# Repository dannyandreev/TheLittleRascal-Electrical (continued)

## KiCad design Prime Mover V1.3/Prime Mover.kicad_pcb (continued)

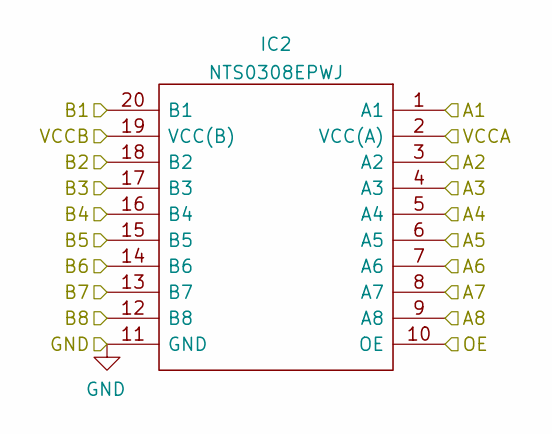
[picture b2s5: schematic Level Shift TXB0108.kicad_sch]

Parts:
IC2: NTS0308EPWJ; SOP65P640X110-20N; Manufacturer_Part_Number NTS0308EPWJ; Mouser Part Number 771-NTS0308EPWJ

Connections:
+3V3: IC2.2 (VCC(A)); also elsewhere on the board
+5V: IC2.19 (VCC(B)); also elsewhere on the board
B3: IC2.17 (B3); also elsewhere on the board
B4: IC2.16 (B4); also elsewhere on the board
B5: IC2.15 (B5); also elsewhere on the board
B6: IC2.14 (B6); also elsewhere on the board
ECHO_3V3: IC2.1 (A1); also elsewhere on the board
ECHO_5V: IC2.20 (B1); also elsewhere on the board
GND: IC2.11 (GND); also elsewhere on the board
GPIO19: IC2.4 (A3); also elsewhere on the board
GPIO20: IC2.5 (A4); also elsewhere on the board
GPIO26: IC2.6 (A5); also elsewhere on the board
GPIO27: IC2.7 (A6); also elsewhere on the board
LVL_OE: IC2.10 (OE); also elsewhere on the board
PWM_ESC: IC2.8 (A7); also elsewhere on the board
PWM_ESC_5V: IC2.13 (B7); also elsewhere on the board
PWM_Servo: IC2.9 (A8); also elsewhere on the board
PWM_Servo_5V: IC2.12 (B8); also elsewhere on the board
TRIG_3V3: IC2.3 (A2); also elsewhere on the board
TRIG_5V: IC2.18 (B2); also elsewhere on the board

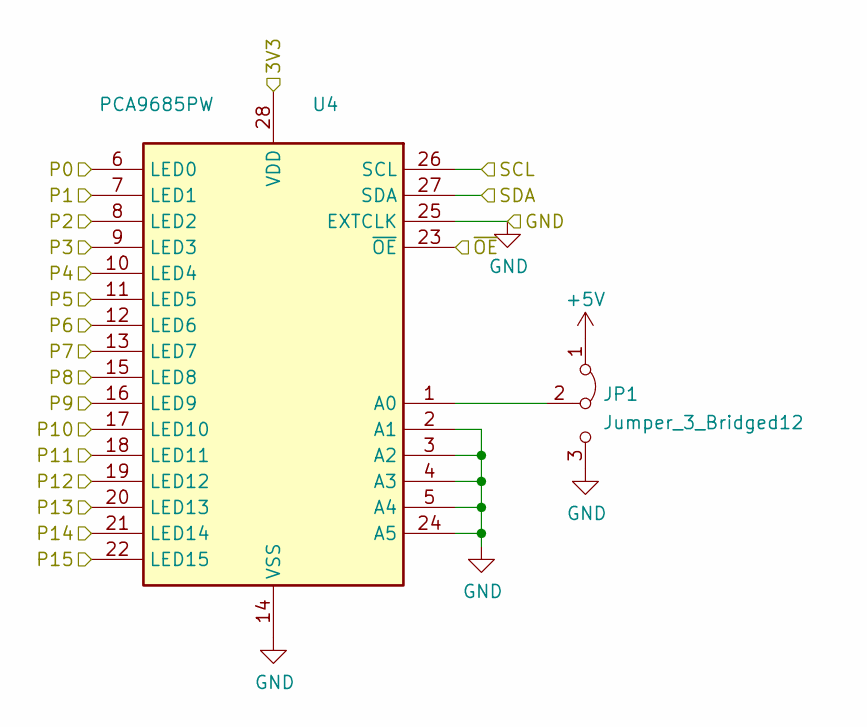
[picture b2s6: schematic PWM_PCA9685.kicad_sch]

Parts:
JP1: Jumper_3_Bridged12; PinHeader_1x03_P2.54mm_Vertical
U4: PCA9685PW; TSSOP-28_4.4x9.7mm_P0.65mm

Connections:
+3V3: U4.28 (VDD); also elsewhere on the board
+5V: JP1.1 (A); also elsewhere on the board
/PWM_PCA9685/P0: U4.6 (LED0); also elsewhere on the board
/PWM_PCA9685/P1: U4.7 (LED1); also elsewhere on the board
/PWM_PCA9685/P2: U4.8 (LED2); also elsewhere on the board
/PWM_PCA9685/P3: U4.9 (LED3); also elsewhere on the board
/PWM_PCA9685/P4: U4.10 (LED4); also elsewhere on the board
/PWM_PCA9685/P5: U4.11 (LED5); also elsewhere on the board
/PWM_PCA9685/P6: U4.12 (LED6); also elsewhere on the board
/PWM_PCA9685/P7: U4.13 (LED7); also elsewhere on the board
/PWM_PCA9685/P8: U4.15 (LED8); also elsewhere on the board
/PWM_PCA9685/P9: U4.16 (LED9); also elsewhere on the board
/PWM_PCA9685/P10: U4.17 (LED10); also elsewhere on the board
/PWM_PCA9685/P11: U4.18 (LED11); also elsewhere on the board
/PWM_PCA9685/P12: U4.19 (LED12)
/PWM_PCA9685/P13: U4.20 (LED13)
GND: JP1.3 (B), U4.2 (A1), U4.3 (A2), U4.4 (A3), U4.5 (A4), U4.14 (VSS), U4.24 (A5), U4.25 (EXTCLK); also elsewhere on the board
I2C_SCL: U4.26 (SCL); also elsewhere on the board
I2C_SDA: U4.27 (SDA); also elsewhere on the board
unnamed: JP1.2 (C), U4.1 (A0)
PWM_ESC: U4.22 (LED15); also elsewhere on the board
PWM_Servo: U4.21 (LED14); also elsewhere on the board
PWM_~OE: U4.23 (~OE); also elsewhere on the board

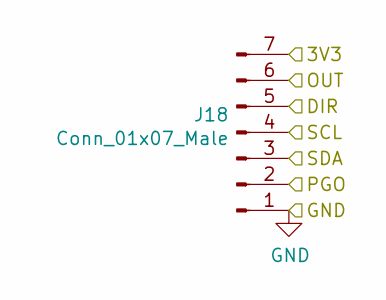
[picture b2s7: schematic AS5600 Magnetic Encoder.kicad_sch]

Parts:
J18: Conn_01x07_Male; JST_PH_B7B-PH-K_1x07_P2.00mm_Vertical

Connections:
+3V3: J18.7; also elsewhere on the board
DIR: J18.5; also elsewhere on the board
ENC_OUT: J18.6; also elsewhere on the board
GND: J18.1; also elsewhere on the board
I2C_SCL: J18.4; also elsewhere on the board
I2C_SDA: J18.3; also elsewhere on the board
PGO: J18.2; also elsewhere on the board

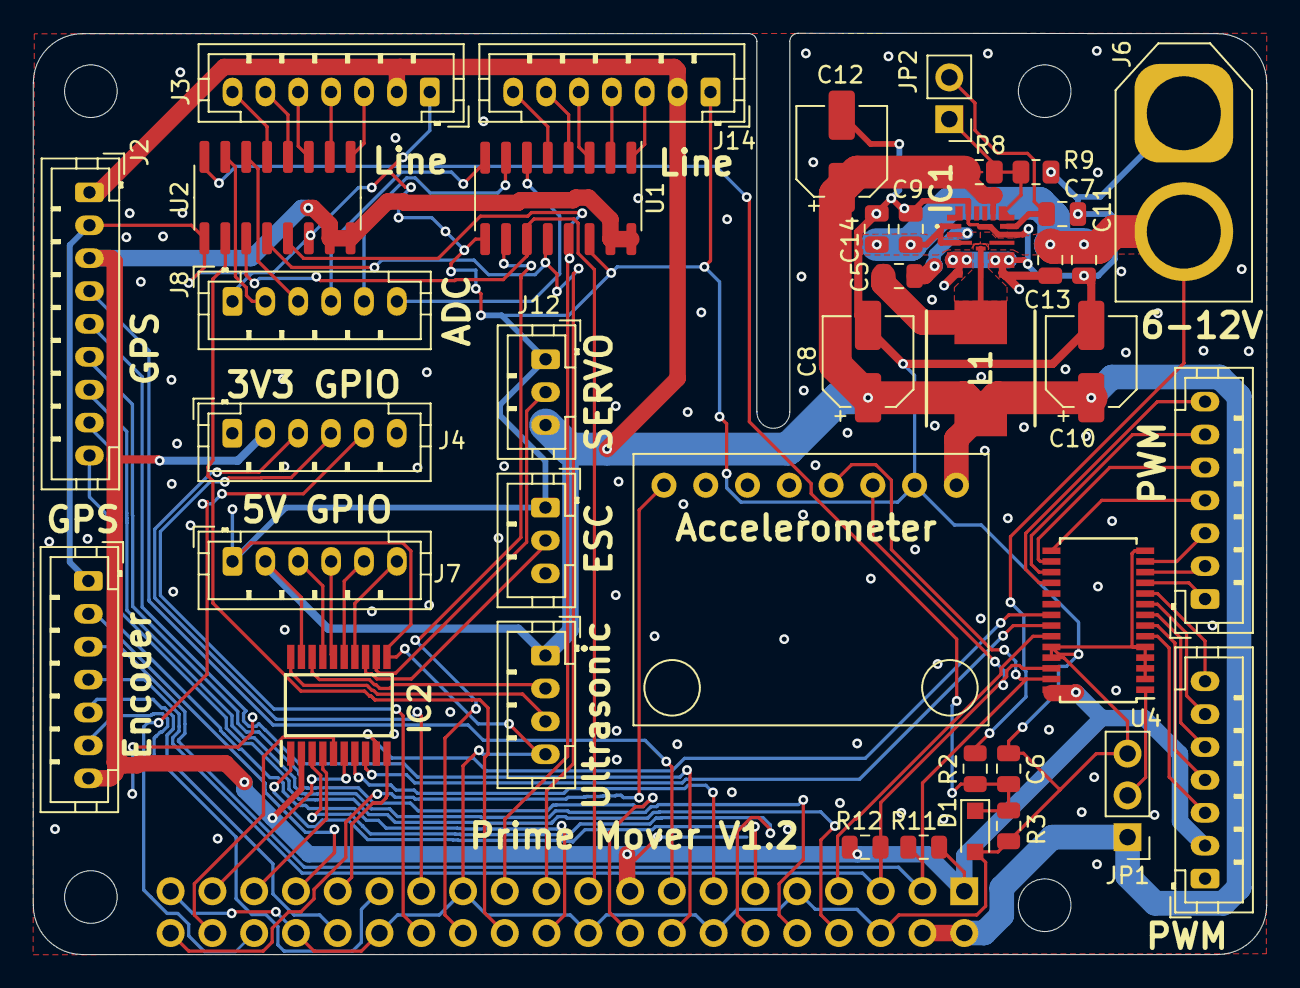
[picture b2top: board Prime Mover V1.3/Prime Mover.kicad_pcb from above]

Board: 2 copper layers, 75.0 x 56.0 mm, 44 parts (1 on the bottom side), 76 nets.

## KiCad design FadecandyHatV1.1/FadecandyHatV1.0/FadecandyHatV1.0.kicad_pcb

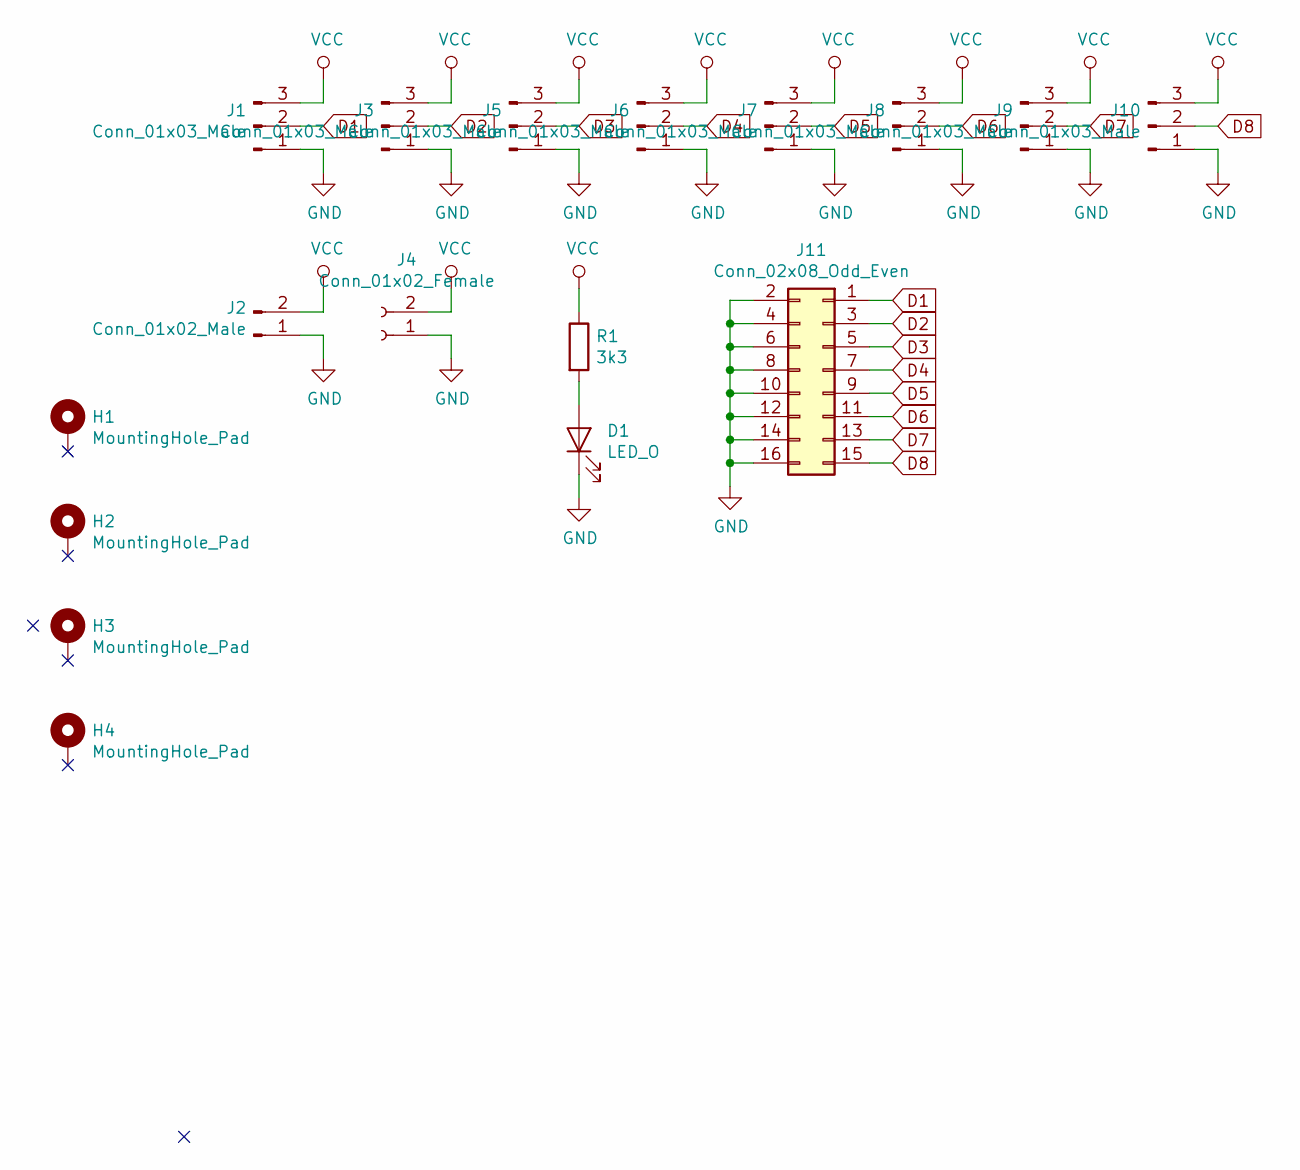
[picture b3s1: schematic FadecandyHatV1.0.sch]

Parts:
D1: LED_O; LED_0805_2012Metric
H1, H2, H3, H4: MountingHole_Pad; MountingHole_3mm
J1, J3, J5, J6, J7, J8, J9, J10: Conn_01x03_Male; JST_PH_B3B-PH-K_1x03_P2.00mm_Vertical
J2: Conn_01x02_Male; AMASS_XT30U-M_1x02_P5.0mm_Vertical
J4: Conn_01x02_Female; AMASS_XT30U-F_1x02_P5.0mm_Vertical
J11: Conn_02x08_Odd_Even; PinHeader_2x08_P2.54mm_Vertical
R1: 3k3; R_0805_2012Metric

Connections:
D1: J1.2, J11.1
D2: J3.2, J11.3
D3: J5.2, J11.5
D4: J6.2, J11.7
D5: J7.2, J11.9
D6: J8.2, J11.11
D7: J9.2, J11.13
D8: J10.2, J11.15
GND: D1.1 (K), J1.1, J2.1, J3.1, J4.1, J5.1, J6.1, J7.1, J8.1, J9.1, J10.1, J11.2, J11.4, J11.6, J11.8, J11.10, J11.12, J11.14, J11.16
unnamed: D1.2 (A), R1.2
VCC: J1.3, J2.2, J3.3, J4.2, J5.3, J6.3, J7.3, J8.3, J9.3, J10.3, R1.1

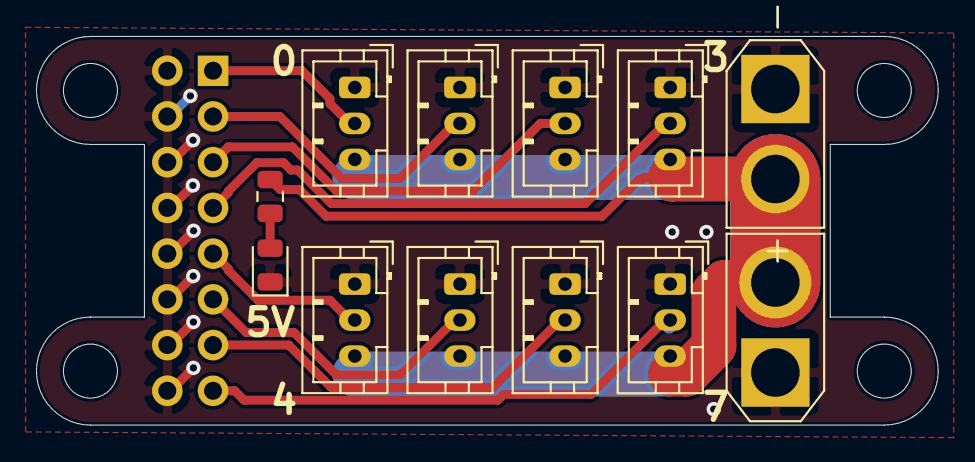
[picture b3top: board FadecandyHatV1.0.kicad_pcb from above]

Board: 2 copper layers, 50.1 x 21.6 mm, 17 parts (1 on the bottom side), 11 nets.

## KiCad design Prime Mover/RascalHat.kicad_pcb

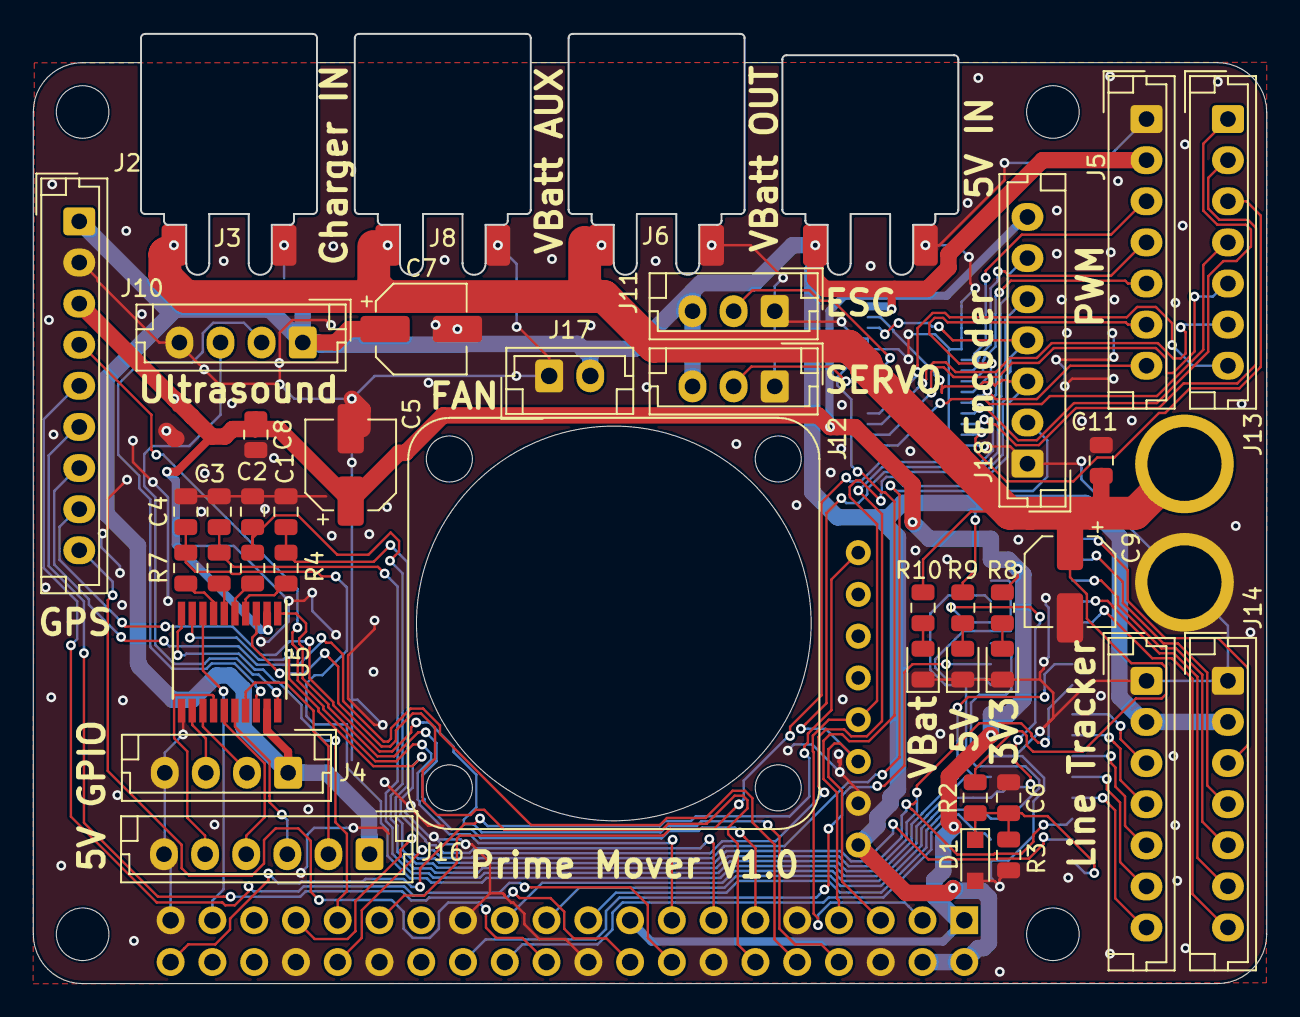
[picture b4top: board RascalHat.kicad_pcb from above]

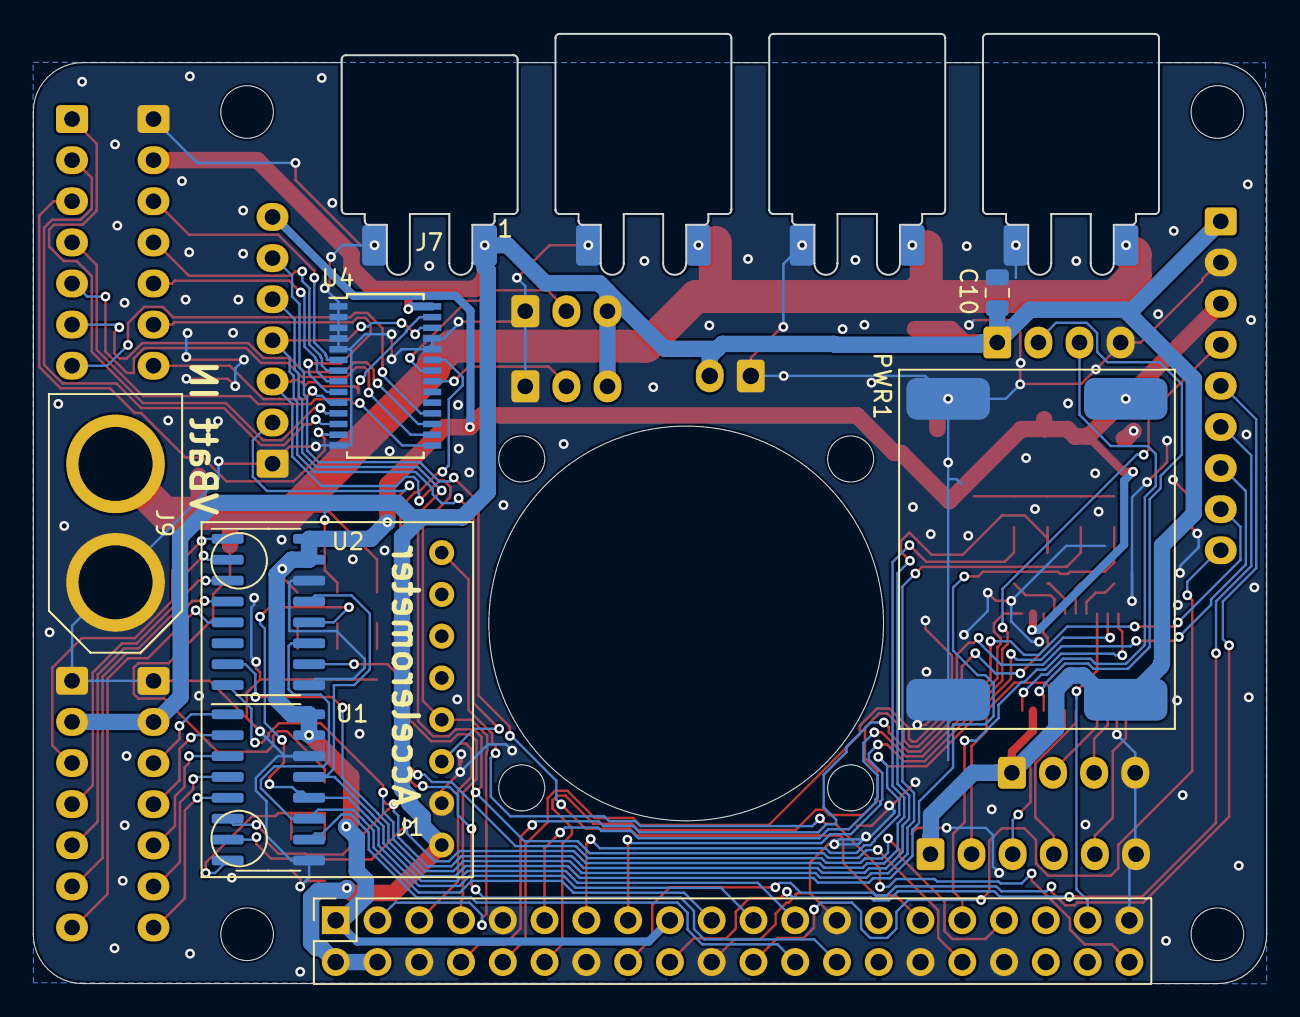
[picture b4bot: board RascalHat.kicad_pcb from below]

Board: 2 copper layers, 74.9 x 57.7 mm, 53 parts (9 on the bottom side), 71 nets.

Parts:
C1, C2, C3, C4, C6, C8, C10, C11: 0.1uF; C_0805_2012Metric
C5, C7, C9: 27uF 16V; CP_Elec_5x5.3
D1: 3V6; D_SOD-323_HandSoldering
D2, D3, D4: LED; D_0805_2012Metric
FAN1: FAN; 25mm-FAN
H1, H2, H3, H4: MountingHole; MountingHole_3.2mm_M3
J1: Conn_01x08_Male; MPU-6050-Module
J2: Conn_01x09_Male; JST_EH_B9B-EH-A_1x09_P2.50mm_Vertical
J3, J6, J8: Conn_01x02_Male; XT30U-M-Horizontal
J4, J10: Conn_01x04_Male; JST_EH_B4B-EH-A_1x04_P2.50mm_Vertical
J5, J13, J14, J15, J18: Conn_01x07_Male; JST_EH_B7B-EH-A_1x07_P2.50mm_Vertical
J7: Conn_01x02_Female; XT30U-F-Horizontal
J9: Conn_01x02_Male; XT60-M
J11, J12: Conn_01x03_Male; JST_EH_B3B-EH-A_1x03_P2.50mm_Vertical
J16: Conn_01x06_Male; JST_EH_B6B-EH-A_1x06_P2.50mm_Vertical
J17: Conn_01x02_Male; JST_EH_B2B-EH-A_1x02_P2.50mm_Vertical
PWR1: MP1584_3V3Module; MP1584-Jacobs-Parts-Module
R1: Raspberry_Pi_2_3; PinSocket_2x20_P2.54mm_Vertical
R2: 4.7k; R_0805_2012Metric
R3: 1.5k; R_0805_2012Metric
R4, R5, R6, R7: 10k; R_0805_2012Metric
R8: 470; R_0805_2012Metric
R9: 2k2; R_0805_2012Metric
R10: 3k3; R_0805_2012Metric
U1, U2: MCP3008-I_P; SOIC-16_3.9x9.9mm_P1.27mm
U4: PCA9685PW; TSSOP-28_4.4x9.7mm_P0.65mm
U5: TXB0108PWR; TSSOP-20_4.4x6.5mm_P0.65mm

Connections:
+3V3: C5.1, C8.1, J2.3, J18.7, PWR1.3, R1.1, R1.17, R8.1, U1.15, U1.16, U2.15, U2.16, U5.2
+5V: C7.1, C10.1, J1.1, J2.1, J4.1, J5.2, J7.1, J10.1, J11.3, J12.3, J14.2, J15.2, J16.1, J17.2, PWR1.2, R1.2, R1.4, R9.1, U4.28, U5.19
+BATT: C9.1, C11.1, J3.2, J6.2, J8.2, J9.2, R2.1, R10.1
/Level Shift TXB0108/B3: J16.2, U5.17
/Level Shift TXB0108/B4: J16.3, U5.16
/Level Shift TXB0108/B5: J16.4, U5.15
/Level Shift TXB0108/B6: J16.5, U5.14
/MCP3008/ADC0_CH6: C4.1, R7.2, U2.7
/MCP3008/ADC0_CH7: C3.1, R6.2, U2.8
/MCP3008/ADC1_CH5: C2.1, R5.2, U1.6
/MCP3008/ADC1_CH6: C1.1, R4.2, U1.7
/PWM_PCA9685/P0: J5.3, U4.6
/PWM_PCA9685/P1: J5.4, U4.7
/PWM_PCA9685/P2: J5.5, U4.8
/PWM_PCA9685/P3: J5.6, U4.9
/PWM_PCA9685/P4: J5.7, U4.10
/PWM_PCA9685/P5: J13.1, U4.11
/PWM_PCA9685/P6: J13.2, U4.12
/PWM_PCA9685/P7: J13.3, U4.13
/PWM_PCA9685/P8: J13.4, U4.15
/PWM_PCA9685/P9: J13.5, U4.16
/PWM_PCA9685/P10: J13.6, U4.17
/PWM_PCA9685/P11: J13.7, U4.18
A7: R1.37, U5.8
A8: R1.13, U5.9
B7: J4.2, U5.13
B8: J4.3, U5.12
CH1_A: R4.1, U5.4
CH2_A: R5.1, U5.5
CH3_A: R6.1, U5.6
CH4_A: R7.1, U5.7
DIR: J18.5, R1.32
ECHO_3V3: R1.11, U5.1
ECHO_5V: J10.3, U5.20
ENC_OUT: J18.6, R1.29
GND: C1.2, C2.2, C3.2, C4.2, C5.2, C6.2, C7.2, C8.2, C9.2, C10.2, C11.2, D1.2, D2.1, D3.1, D4.1, J1.2, J2.2, J3.1, J4.4, J5.1, J6.1, J7.2, J8.1, J9.1, J10.4, J11.1, J12.1, J14.1, J15.1, J16.6, J17.1, J18.1, PWR1.1, PWR1.4, R1.6, R1.9, R1.14, R1.20, R1.25, R1.30, R1.34, R1.39, R3.2, U1.9, U1.14, U2.9, U2.14, U4.1, U4.2, U4.3, U4.4, U4.5, U4.14, U4.24, U4.25, U5.11
GPIO21: J1.8, R1.40
GPS_DTR: J2.4, R1.15
GPS_PWR: J2.5, R1.16
GPS_RI: J2.6, R1.18
GPS_RST: J2.9, R1.22
GPS_RX: J2.8, R1.8
GPS_TX: J2.7, R1.10
I2C_SCL: J1.3, J18.4, R1.5, U4.26
I2C_SDA: J1.4, J18.3, R1.3, U4.27
LVL_OE: R1.31, U5.10
unnamed: D2.2, R8.2
unnamed: D3.2, R9.2
unnamed: D4.2, R10.2
unnamed: J14.3, U2.1
unnamed: J14.4, U2.2
unnamed: J14.5, U2.3
unnamed: J14.6, U2.4
unnamed: J14.7, U2.5
unnamed: J15.3, U1.1
unnamed: J15.4, U1.2
unnamed: J15.5, U1.3
unnamed: J15.6, U1.4
unnamed: J15.7, U1.5
PGO: J18.2, R1.33
PWM_ESC: J11.2, U4.22
PWM_Servo: J12.2, U4.21
PWM_~OE: R1.7, U4.23
SPI_CLK: R1.23, U1.13, U2.13
SPI_CS_ADC0: R1.26, U2.10
SPI_CS_ADC1: R1.24, U1.10
SPI_MISO: R1.21, U1.12, U2.12
SPI_MOSI: R1.19, U1.11, U2.11
TRIG_3V3: R1.12, U5.3
TRIG_5V: J10.2, U5.18
VBAT_Read: C6.1, D1.1, R2.2, R3.1, U1.8

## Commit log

2021-09-09 Update issue templates
    created issues template
2021-09-21 Add files via upload
    Added schematic files
2021-09-21 re-committing schematic to keep file hierarchy
2021-10-05 update schematic
2021-10-19 ...tweaking schematic....
2021-10-19 everything except accelerometer done
2021-10-22 using only connector for accelerometer
2021-10-23 fade candy pcb done
2021-10-23 added extra adc
2021-10-24 schematic updated
2021-10-25 corruption change
2021-10-31 schematic done, symbol-footprint done, pcb started
2021-10-31 schematic updated, all footprints created, pcb layout started
2021-11-01 schematic capacitors added, pcb done, gerbers generated
2021-11-04 pcb XT60 location adjusted, i2C pullup resistors added
2021-11-15 V1.1 Created, updated connectors on fadecandy and prime mover. changed fan mounting holes
2021-12-15 V1.1 Manufactured
2021-12-15 Rascal hat pcb (#10)
    * pcb XT60 location adjusted, i2C pullup resistors added
    * V1.1 Created, updated connectors on fadecandy and prime mover. changed fan mounting holes
    * V1.1 Manufactured
2022-01-18 end of work 2021
2022-01-18 Rascal hat pcb (#11)
    * pcb XT60 location adjusted, i2C pullup resistors added
    * V1.1 Created, updated connectors on fadecandy and prime mover. changed fan mounting holes
    * V1.1 Manufactured
    * end of work 2021
2022-01-23 first revision of V1.2 done
2022-02-22 polished
2022-02-22 Pihat polish (#16)
    * first revision of V1.2 done
    * polished
2022-07-29 Prime Mover V1.4
2022-07-29 Pihat polish (#17)
    * first revision of V1.2 done
    * polished
    * Prime Mover V1.4
2022-08-15 V1.5 done
2022-08-15 Pihat polish (#18)
    * first revision of V1.2 done
    * polished
    * Prime Mover V1.4
    * V1.5 done
2022-11-23 PCBA quoted - generated BOM & POS
2022-11-23 BOM file updated
2022-11-23 V1.6 (#19)
    * PCBA quoted - generated BOM & POS
    * BOM file updated
